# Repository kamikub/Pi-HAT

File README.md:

# PiHat_Group18

This is Group 18's Git repo, containing all relevant documentation, schematic, PCB and simulation files for the design of our PiHat.

The PiHat we designed is a frequency tuner: the user will be able to select a desired sound-frequency or pitch to listen for via a series of push buttons and through the operation of an onboard microphone, instrumentation op-amp and code written to the Pi, the PiHat will indicate whether the desired frequency is acquired or not (using LED's and a buzzer).

This repo includes all schematics, PCB, simulations and other relevant documentation that went into the design of this PiHat. For the most part, this was a modular design process – our PiHat was broken down into three submodules: power supply, LED/buzzer interface and operational amplifier. These submodules were individually designed and simulated on LTSpice and KiCad. The integration of all three submodules was developed on KiCad by means of a final PCB design of the PiHat as a whole.

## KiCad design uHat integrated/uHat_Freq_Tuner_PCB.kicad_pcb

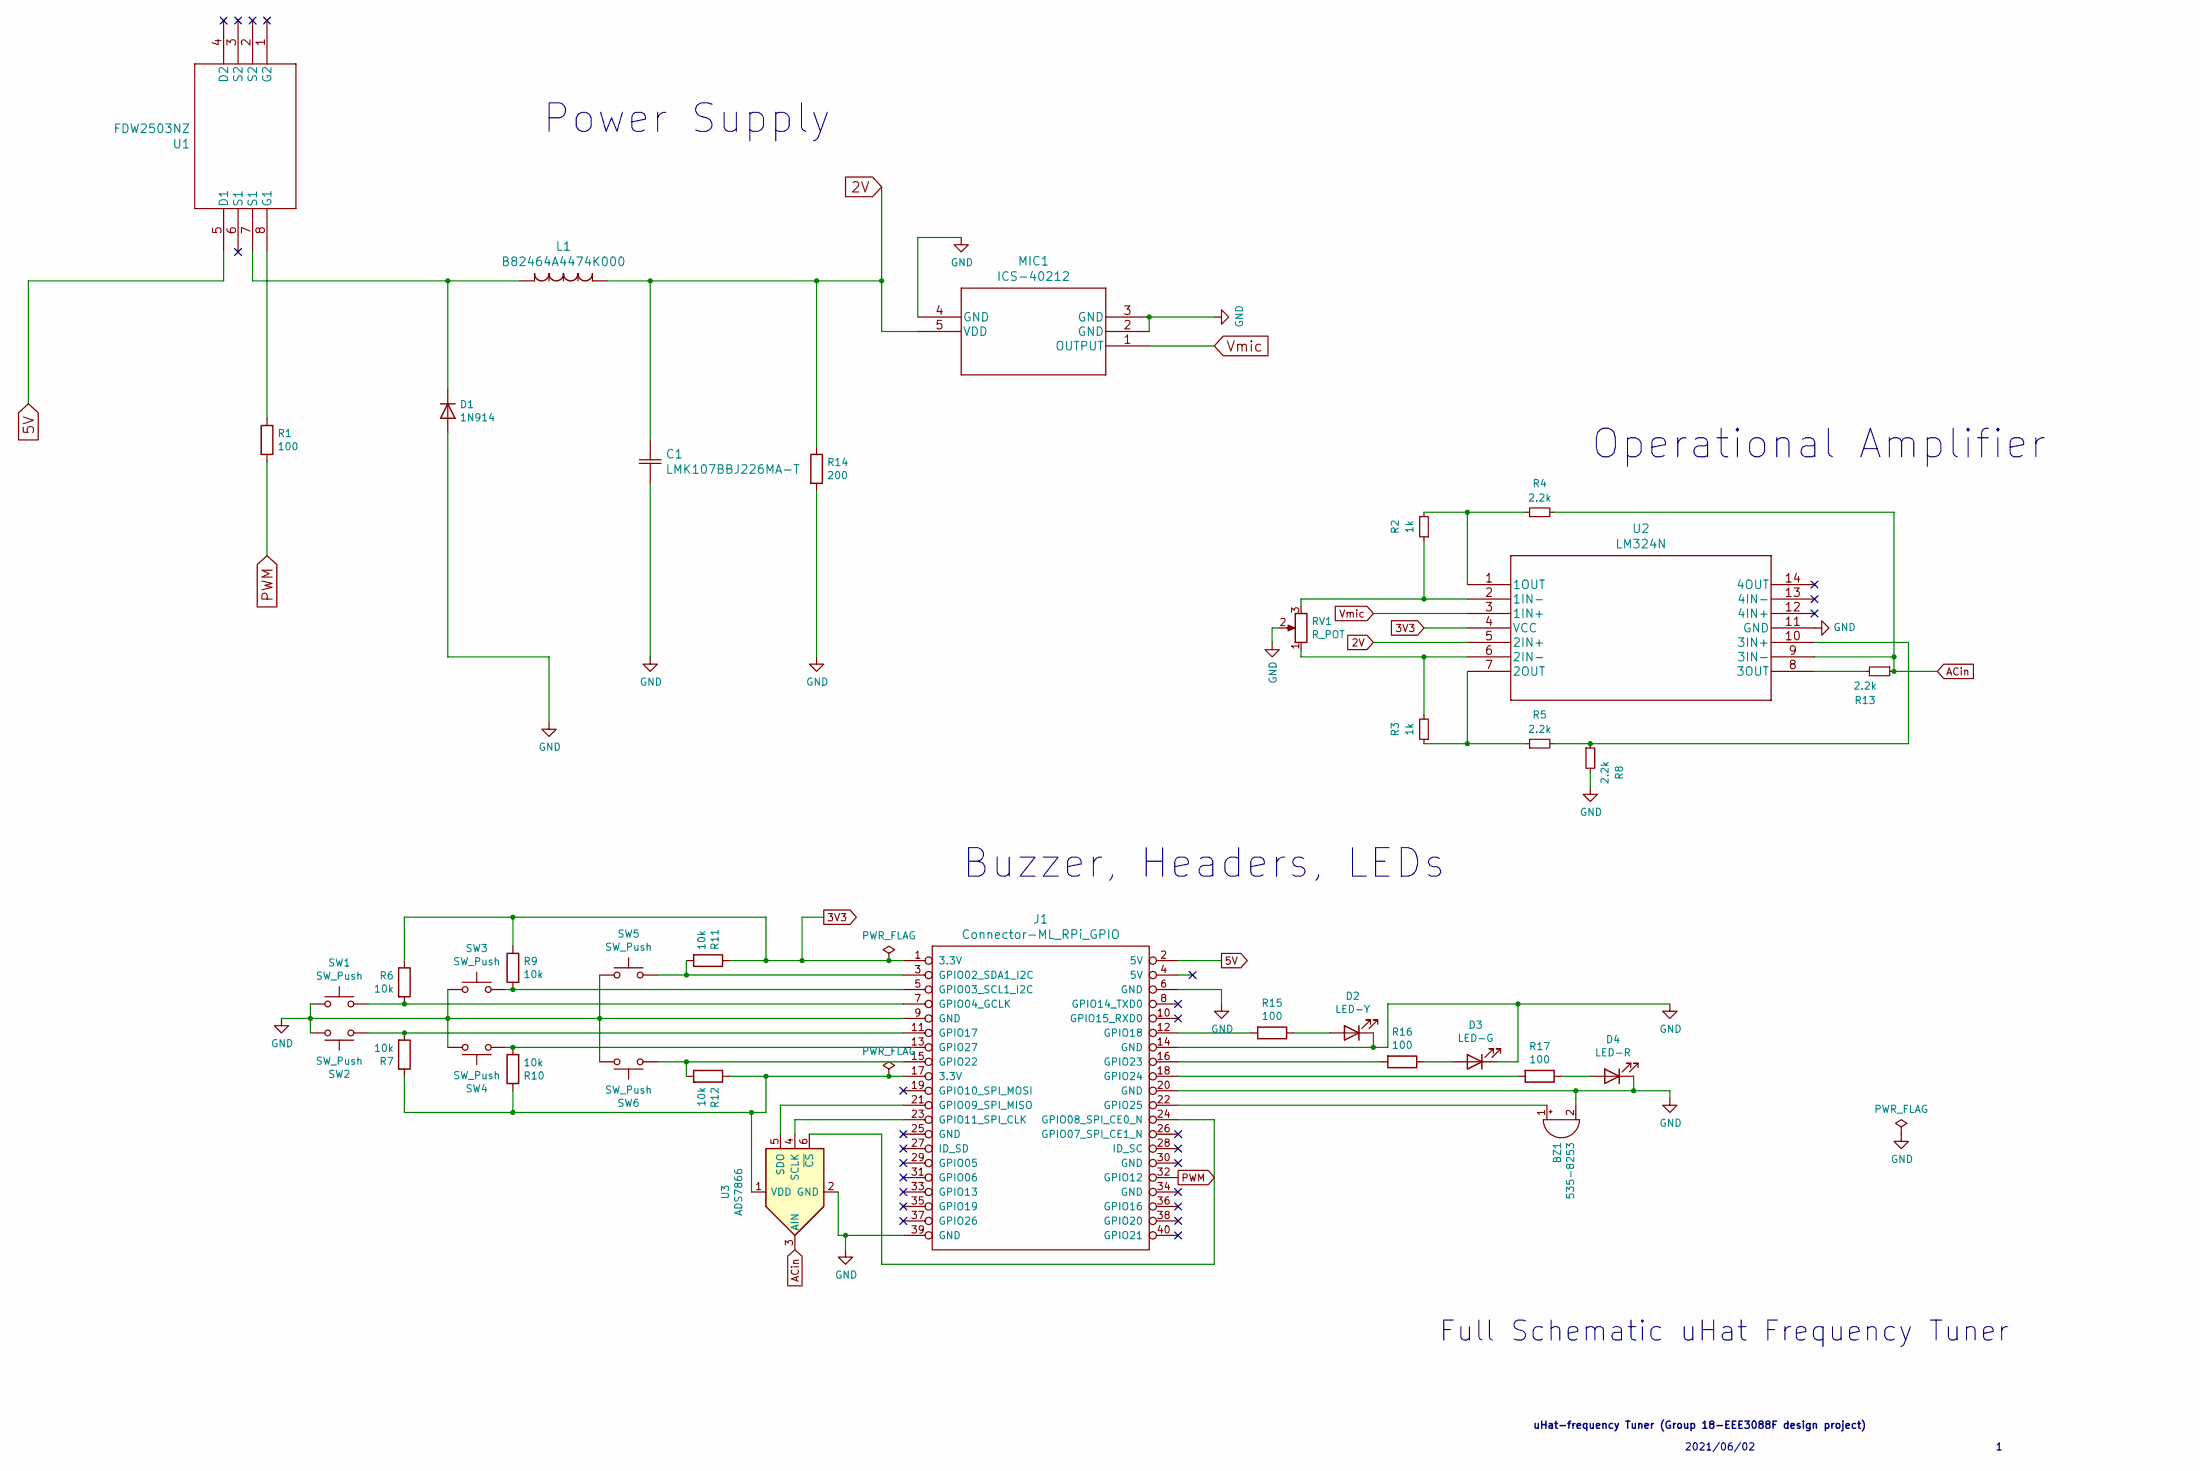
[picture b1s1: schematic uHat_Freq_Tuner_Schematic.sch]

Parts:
BZ1: 535-8253; Buzzer_15x7.5RM7.6
C1: LMK107BBJ226MA-T
D1: 1N914; D_0201_0603Metric
D2: LED-Y; LED_0402_1005Metric_Pad0.77x0.64mm_HandSolder
D3: LED-G; LED_0402_1005Metric_Pad0.77x0.64mm_HandSolder
D4: LED-R; LED_0402_1005Metric_Pad0.77x0.64mm_HandSolder
J1: Connector-ML_RPi_GPIO; Samtec_HLE-120-02-xxx-DV-BE-A_2x20_P2.54mm_Horizontal
L1: B82464A4474K000
MIC1: ICS-40212
R1, R15, R16, R17: 100; R_0201_0603Metric_Pad0.64x0.40mm_HandSolder
R2, R3: 1k; R_0201_0603Metric_Pad0.64x0.40mm_HandSolder
R4, R5, R8, R13: 2.2k; R_0201_0603Metric_Pad0.64x0.40mm_HandSolder
R6, R7, R9, R10, R11, R12: 10k; R_0201_0603Metric_Pad0.64x0.40mm_HandSolder
R14: 200; R_0201_0603Metric_Pad0.64x0.40mm_HandSolder
RV1: R_POT; Potentiometer_ACP_CA6-VSMD_Vertical
SW1, SW2, SW3, SW4, SW5, SW6: SW_Push; 1825910-6
U1: FDW2503NZ
U2: LM324N
U3: ADS7866; ADS7866IDBVT

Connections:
2V: C1.1, L1.1, MIC1.5 (VDD), R14.1, U2.5 (2IN+)
3V3: J1.1 (3.3V), R6.1, R9.1, R11.1, U2.4 (VCC)
5V: J1.2 (5V), U1.5 (D1)
ACin: R4.2, R13.1, U2.9 (3IN-), U3.3 (AIN)
GND: BZ1.2 (+), C1.2, D1.2 (A), D2.1 (K), D3.1 (K), D4.1 (K), J1.6 (GND), J1.9 (GND), J1.14 (GND), J1.20 (GND), J1.39 (GND), MIC1.2 (GND), MIC1.3 (GND), MIC1.4 (GND), R8.2, R14.2, RV1.2, SW1.2, SW2.2, SW3.1, SW4.1, SW5.1, SW6.1, U2.11 (GND), U3.2 (GND)
unnamed: BZ1.1 (-), J1.22 (GPIO25)
unnamed: D1.1 (K), L1.2, U1.7 (S1)
unnamed: D2.2 (A), R15.1
unnamed: D3.2 (A), R16.1
unnamed: D4.2 (A), R17.1
unnamed: J1.3 (GPIO02_SDA1_I2C), R11.2, SW5.2
unnamed: J1.5 (GPIO03_SCL1_I2C), R9.2, SW3.2
unnamed: J1.7 (GPIO04_GCLK), R6.2, SW1.1
unnamed: J1.11 (GPIO17), R7.2, SW2.1
unnamed: J1.12 (GPIO18), R15.2
unnamed: J1.13 (GPIO27), R10.2, SW4.2
unnamed: J1.15 (GPIO22), R12.2, SW6.2
unnamed: J1.16 (GPIO23), R16.2
unnamed: J1.17 (3.3V), R7.1, R10.1, R12.1, U3.1 (VDD)
unnamed: J1.18 (GPIO24), R17.2
unnamed: J1.21 (GPIO09_SPI_MISO), U3.5 (SDO)
unnamed: J1.23 (GPIO11_SPI_CLK), U3.4 (SCLK)
unnamed: J1.24 (GPIO08_SPI_CE0_N), U3.6 (~CS)
unnamed: R1.1, U1.8 (G1)
unnamed: R2.1, RV1.3, U2.2 (1IN-)
unnamed: R2.2, R4.1, U2.1 (1OUT)
unnamed: R3.1, R5.1, U2.7 (2OUT)
unnamed: R3.2, RV1.1, U2.6 (2IN-)
unnamed: R5.2, R8.1, U2.10 (3IN+)
unnamed: R13.2, U2.8 (3OUT)
PWM: J1.32 (GPIO12), R1.2
Vmic: MIC1.1 (OUTPUT), U2.3 (1IN+)

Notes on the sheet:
2021/06/02
Full Schematic uHat Frequency Tuner
uHat-frequency Tuner (Group 18-EEE3088F design project)
Operational Amplifier
Buzzer, Headers, LEDs
Power Supply

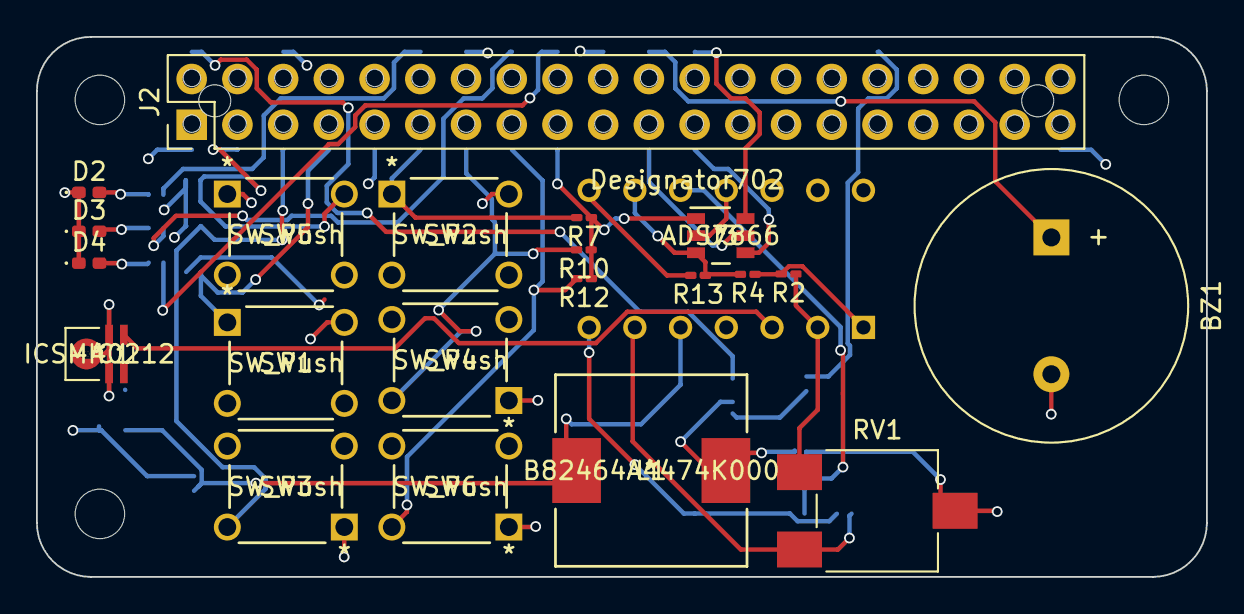
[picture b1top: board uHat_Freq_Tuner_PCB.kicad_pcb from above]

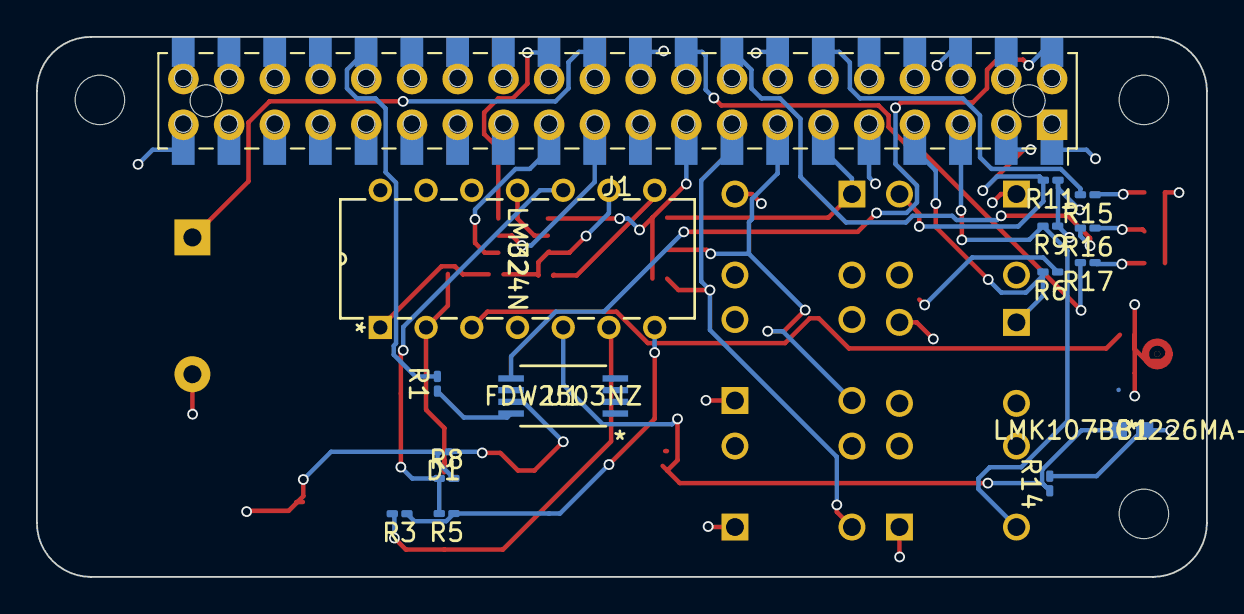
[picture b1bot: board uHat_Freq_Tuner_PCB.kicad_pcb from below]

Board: 4 copper layers, 65.0 x 30.0 mm, 37 parts (16 on the bottom side), 32 nets.

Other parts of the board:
J2: RPi_GPIO; PinHeader_2x20_P2.54mm_Vertical

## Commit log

2021-06-03 Add LICENSE
2021-06-04 Added Schematics folder
2021-06-04 Deleted Schematics
2021-06-04 Add new directory
2021-06-04 Added schematics
2021-06-04 Added LTSpice
2021-06-04 Added KiCad folder
2021-06-04 Added Power Supply to Simulations
2021-06-04 Added Op Amp to simulations
2021-06-04 Added LED folder to simulations
2021-06-04 Upload Power Supply LTSpice schematic
2021-06-04 Removed Folder
2021-06-04 Added Power Supply
2021-06-04 Deleted
2021-06-04 Upload New File
2021-06-04 Add CONTRIBUTING
2021-06-04 Submodule three v1
2021-06-04 Submodule2 first try
2021-06-04 Submodule 3 attempt 2
2021-06-04 Added Components
2021-06-04 Added
2021-06-04 Revert "Added Components"
    This reverts commit 7c3e1872062027e47181b567b89790c09e809150
2021-06-04 Tracking downloads
2021-06-04 Updated contributing file
2021-06-04 Upload of J1 PI header schematic
2021-06-04 Upload J1 PI header footprint
2021-06-04 Upload U1 quad op-amp footprint
2021-06-04 Upload U1 quad op-amp schematic
2021-06-05 Upload of new microphone component
2021-06-05 Upload of new microphone
2021-06-05 Replace IntegratedCircuit.PNG
2021-06-05 Replace PowerSupply.PNG
2021-06-05 Upload Instrumentation Amplifier
2021-06-05 Upload Headers, Buzzer and LEDs
2021-06-05 Upload Project Assignment 3 Folder containing all necessary files
2021-06-05 Upload of the project assignement 3 PCB file
2021-06-05 Replace Project assignement 3 PCB file with correct one
2021-06-05 Update CONTRIBUTING.md (include download instructions)
2021-06-09 Replace PowerSupply.sch
2021-06-10 Add new file
2021-06-10 Upload LM324N Quad-amplifier datasheet
2021-06-10 Upload of amplifier circuit schematic
2021-06-10 Upload of amplifier input signals V1(mic signal) and V2(power regulator)
2021-06-10 Upload of generic amplifier output
2021-06-10 Upload of output after an increase fluctuation in V2(power regulator)
2021-06-10 Upload of output after increase in potentiometer resistance
2021-06-11 Add How-To for use of amplifier subsystem 3
2021-06-11 Upload uPIHat requirements and specifications
2021-06-11 Uploaded Integrated Circuit
2021-06-11 updating folder
2021-06-11 Deleted temp folder
2021-06-11 Updated folder
2021-06-11 How to guide on the usage of subsystem three.
2021-06-11 Update LED and Pi peripherals How To. and proper naming
2021-06-11 Update LED and Pi periferals How To.md better formatting
2021-06-11 Add a manufacturing guide for the PCB
2021-06-11 Subsystem3(leds etc) v1
2021-06-11 Replace ADCHeaderLEDsbuttons.asc v2 replaced ADC to the better one
2021-06-11 LEDs operational simulation
2021-06-11 Simulation of buttons closed
2021-06-11 open buttons
2021-06-11 LED operation .plt
2021-06-11 closed switch plt
2021-06-11 open switches plt
2021-06-11 ADC datasheet
2021-06-11 RED LED
2021-06-11 Update BOM.md complete
2021-06-11 LED GREEN
2021-06-11 LED Yellow
2021-06-11 Buzzer
2021-06-11 Button
2021-06-11 Add software directory including the code and textfile
2021-06-11 textfile for altering the frequencies
2021-06-11 operating code for the uHat
2021-06-18 Replace OperationalAmplifier.PNG
2021-06-18 Upload submodule 3 dependant File
2021-06-18 Update Instrumentation_tuner_pcb
2021-06-18 Upload Integrated Schematic dependant File
2021-06-18 Add Frequency tuner reference manual

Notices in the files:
parts and their libraries:
Copyright 2016 Accelerated Designs. All rights reserved.
Copyright 2021 Accelerated Designs. All rights reserved.
